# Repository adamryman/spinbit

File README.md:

# SpinBit: A Wearable Rotation Counter
Katie Kemp, Adam Ryman, Isaac Perry
CSE 477, Spring 2015

spinbit is a piece of open source hardware that counts how many time you spin over time and send that data to your android phone.

See the [Final Report](./spinbit-final-report.pdf)

Web page that includes weekly reports: [spinbit.adamryman.com](http://spinbit.adamryman.com)

You can also see our [Poster](./poster.pdf). It was made in powerpoint in the file poster.pptx, and I, Adam, rendered the poster on linux so the fonts in the pdf may be off.

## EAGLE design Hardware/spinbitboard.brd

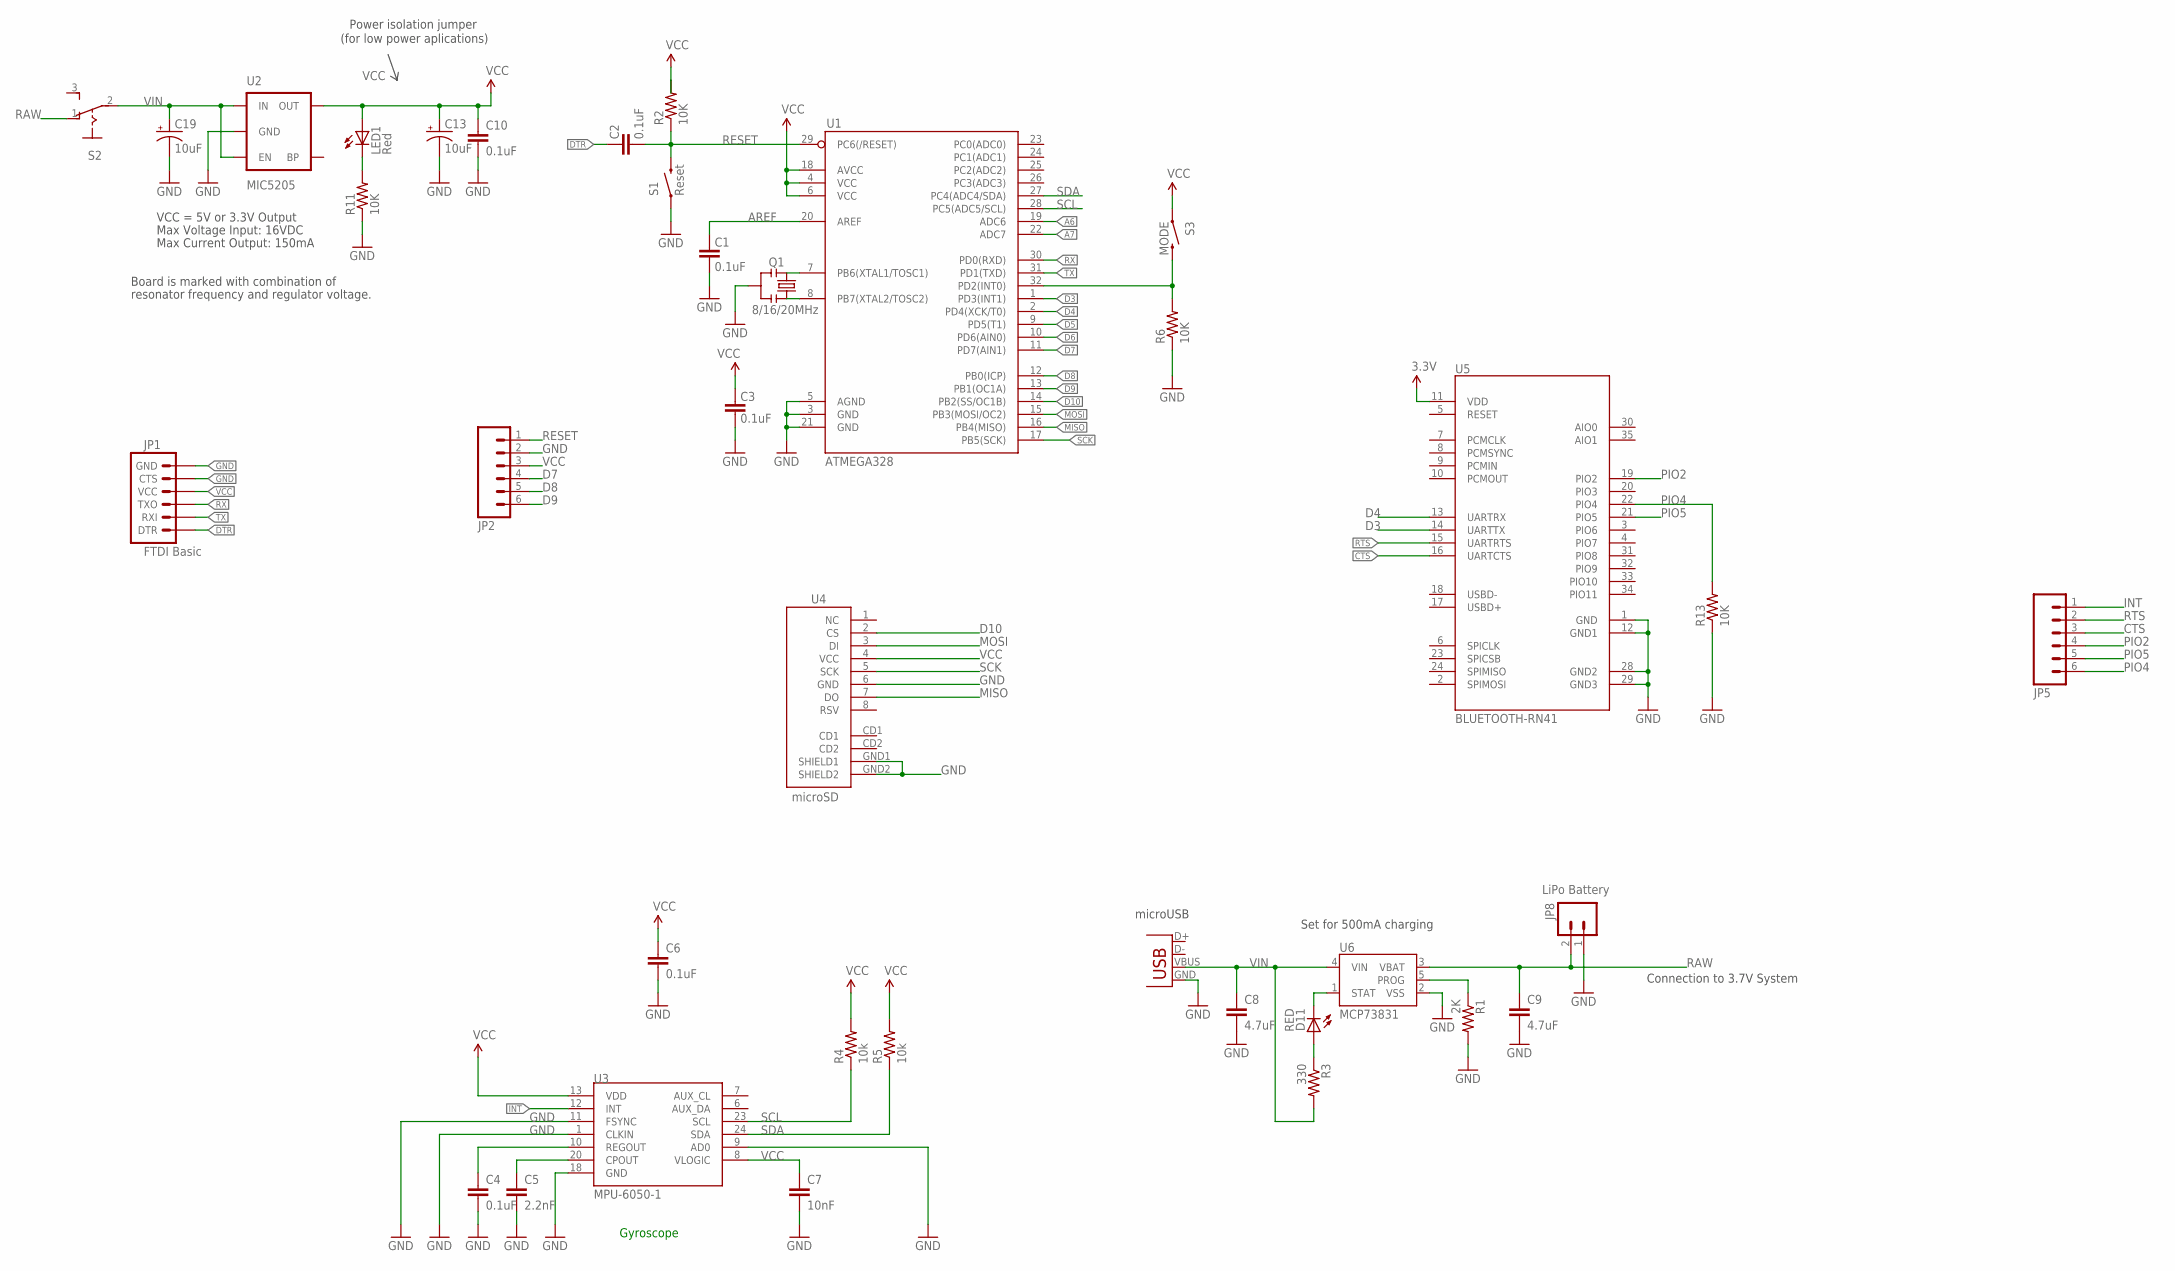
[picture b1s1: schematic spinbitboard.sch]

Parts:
C1, C2, C3, C4, C6, C10: 0.1uF; 0603-CAP
C5: 2.2nF; 0603-CAP
C7: 10nF; 0603-CAP
C8, C9: 4.7uF; C0603
C13, C19: 10uF; EIA3216
D11: RED; LED-0603
JP1: FTDI Basic; 1X06
JP2, JP5: M06SIP; 1X06
JP8: LiPo Battery; JST-2-SMD
LED1: Red; 0603-LED-ALT1
Q1: 8/16/20MHz; RESONATOR-SMD-1:1
R1: 2K; R0603
R2, R6, R11, R13: 10K; 0603-RES
R3: 330; R0603
R4, R5: 10k; 0603-RES
S1: Reset; TACTILE-SWITCH-SMD-ALT01
S2: 255SB
S3: MODE; TACTILE-SWITCH-SMD-ALT01
U1: ATMEGA328; TQFP32-08
U2: MIC5205; SOT23-5
U3: MPU-6050-1; QFN-24-4MM2
U4: microSD; MICRO-SD-SOCKET-PP
U5: BLUETOOTH-RN41; RN41
U6: MCP73831; SOT23-5
X1: Micro USB; USB-MICROB

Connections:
3.3V: C6.1, R4.2, R5.2, S3.1, S3.2 (1), U3.13 (VDD)
A6: U1.19 (ADC6)
A7: U1.22 (ADC7)
AREF: C1.2, U1.20 (AREF)
CTS: JP5.3, U5.16 (UARTCTS)
D2: R6.2, S3.3 (2), S3.4 (2), U1.32 (PD2(INT0))
D3: U1.1 (PD3(INT1)), U5.14 (UARTTX)
D4: U1.2 (PD4(XCK/T0)), U5.13 (UARTRX)
D5: U1.9 (PD5(T1))
D6: U1.10 (PD6(AIN0))
D7: JP2.4, U1.11 (PD7(AIN1))
D8: JP2.5, U1.12 (PB0(ICP))
D9: JP2.6, U1.13 (PB1(OC1A))
D10: U1.14 (PB2(SS/OC1B)), U4.2 (CS)
DTR: C2.2, JP1.1 (DTR)
GND: C1.1, C3.1, C4.2, C5.2, C6.2, C7.2, C8.2, C9.2, C10.2, C13.C (-), C19.C (-), JP1.5 (CTS), JP1.6 (GND), JP2.2, JP8.1, Q1.2, R1.2, R6.1, R11.1, R13.1, S1.1, S1.2 (1), U1.3 (GND), U1.5 (AGND), U1.21 (GND), U2.2 (GND), U3.1 (CLKIN), U3.9 (AD0), U3.11 (FSYNC), U3.18 (GND), U4.6 (GND), U4.GND1 (SHIELD1), U4.GND2 (SHIELD2), U5.1 (GND), U5.12 (GND1), U5.28 (GND2), U5.29 (GND3), U6.2 (VSS), X1.GND
INT: JP5.1, U3.12 (INT)
MISO: U1.16 (PB4(MISO)), U4.7 (DO)
MOSI: U1.15 (PB3(MOSI/OC2)), U4.3 (DI)
unnamed: Q1.3, U1.8 (PB7(XTAL2/TOSC2))
unnamed: Q1.1, U1.7 (PB6(XTAL1/TOSC1))
unnamed: LED1.C, R11.2
unnamed: C5.1, U3.20 (CPOUT)
unnamed: C4.1, U3.10 (REGOUT)
unnamed: D11.A, R3.1
PIO2: JP5.4, U5.19 (PIO2)
PIO4: JP5.6, R13.2, U5.22 (PIO4)
PIO5: JP5.5, U5.21 (PIO5)
PROG: R1.1, U6.5 (PROG)
RAW: C9.1, JP8.2, S2.1 (O), U6.3 (VBAT)
RESET: C2.1, JP2.1, R2.1, S1.3 (2), S1.4 (2), U1.29 (PC6(/RESET))
RTS: JP5.2, U5.15 (UARTRTS)
RX: JP1.3 (TXO), U1.30 (PD0(RXD))
SCK: U1.17 (PB5(SCK)), U4.5 (SCK)
SCL: R4.1, U1.28 (PC5(ADC5/SCL)), U3.23 (SCL)
SDA: R5.1, U1.27 (PC4(ADC4/SDA)), U3.24 (SDA)
STAT: D11.C, U6.1 (STAT)
TX: JP1.2 (RXI), U1.31 (PD1(TXD))
VCC: C3.2, C7.1, C10.1, C13.A (+), JP1.4 (VCC), JP2.3, LED1.A, R2.2, U1.4 (VCC), U1.6 (VCC), U1.18 (AVCC), U2.5 (OUT), U3.8 (VLOGIC), U4.4 (VCC), U5.11 (VDD)
VIN: C8.1, C19.A (+), R3.2, S2.2, U2.1 (IN), U2.3 (EN), U6.4 (VIN), X1.VBUS

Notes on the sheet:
Max Voltage Input: 16VDC
Max Current Output: 150mA
Board is marked with combination of
resonator frequency and regulator voltage.
VCC = 5V or 3.3V Output
Power isolation jumper
(for low power aplications)
Gyroscope
Set for 500mA charging
Connection to 3.7V System
microUSB

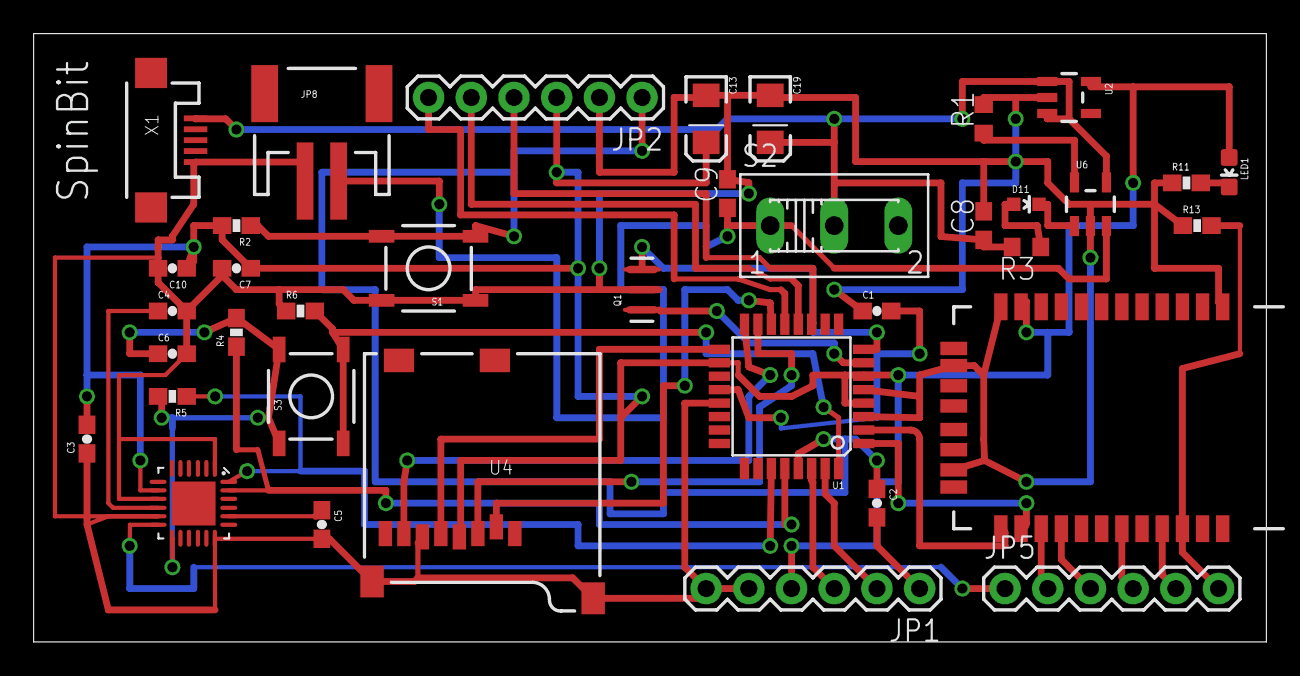
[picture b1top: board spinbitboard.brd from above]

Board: 2 copper layers, 73.3 x 36.2 mm, 37 parts (0 on the bottom side), 36 nets.

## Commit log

2015-04-28 Adding bluetooth code
2015-04-28 Adding open source bluetooth and gyro design files
2015-04-28 Adding Gyro logging to serial
2015-04-28 Added code for writing to SD Card. test, test, test
2015-05-05 Gyro Data writing to SD Card
2015-05-06 Now using better code to configure Gyro also has button on pin 7 to stop writing to sd
2015-05-08 Cleaning up
2015-05-09 Not currently working
2015-05-09 Deleting and bluetooth works
2015-05-09 Forgot to save....
2015-05-20 adding android version 5
2015-05-27 Board Files
2015-05-28 Starting an overhall, branching to avoid bad commits
2015-05-30 Making progress
2015-05-31 everything works
2015-06-02 Adding files that are for spinbit hardware
2016-08-21 Open source ready

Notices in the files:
parts and their libraries:
SparkFun-RF: Licensing: CC v3.0 Share-Alike You are welcome to use this library for commercial purposes.
